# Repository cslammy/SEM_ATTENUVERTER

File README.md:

# SEM_ATTENUVERTER
Audio Attenuverter inspired by classic Tom Oberheim designs

My First experience with an attenuverter--turn a pot CCW, you get increasing amplitude and a signal in phase; CW and you get increasing amplitude with the signal 180 degrees out of phase, was the filter mod pots found an Oberheim SEM. Was I 14 years old? Well, it blew my young mind....Combined with the SEMs multimode filter you can get all sorts of cool sound with the attenuator/inverter + filter, but now, with attenuverters found everywhere, they are, well, everywhere.  This time I used the same core component that made the SEM attenuverter so cool, the somewhat unusual (but not unobtainium) center tapped pot as module's the centerpiece.  Homage to the mighty TO! At noon you get ground--zilch. Turn the pot and you get attenuverter action.  I also added bias offset for each signal, controllable by CV or a set 5V signal. This is an evolving design....it is for +/- 15V "large format" or Frac, but a +/- 12V Euro redesign in is the works.

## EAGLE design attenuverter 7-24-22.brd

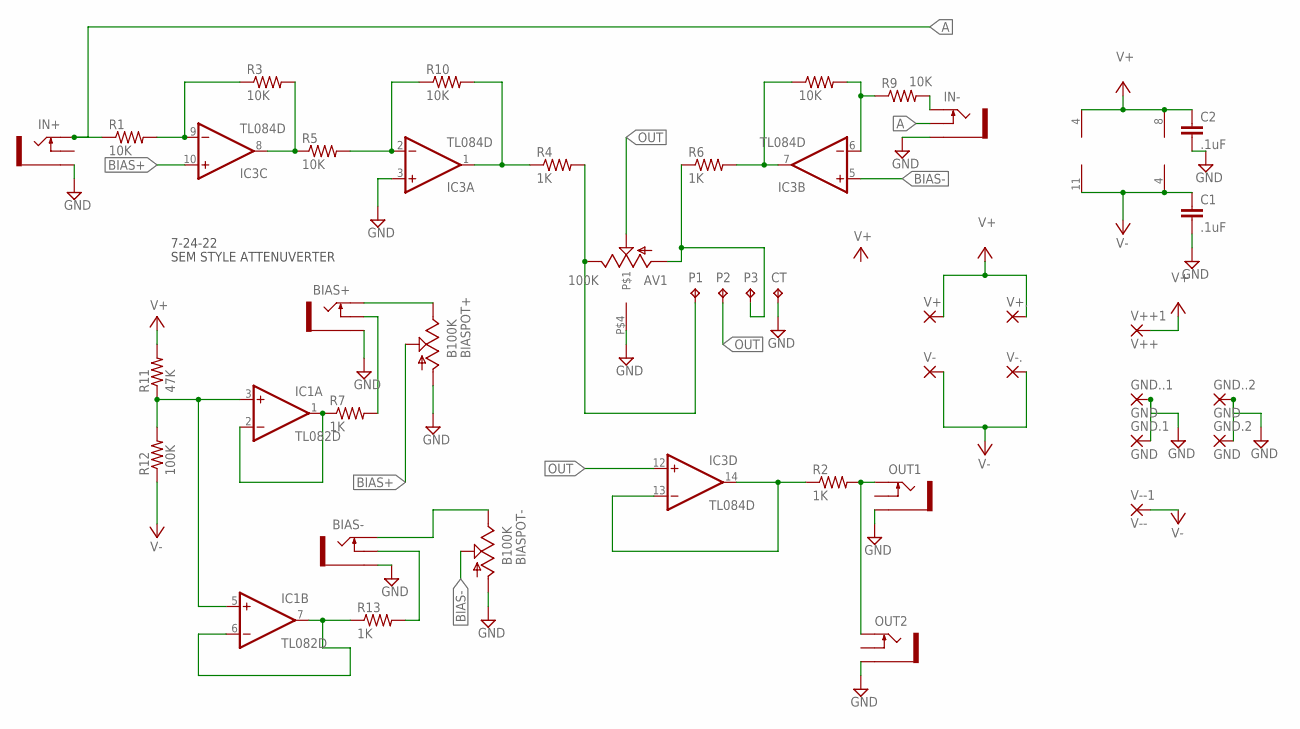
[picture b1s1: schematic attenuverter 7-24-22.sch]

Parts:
AV1: 100K; ALPSCENTERTAP
BIAS+: THONKICONNOLD; THONKICONN
BIAS-: THONKICONNOLD; THONKICONN
BIASPOT+: B100K; 9MM_SNAP-IN_POT
BIASPOT-: B100K; 9MM_SNAP-IN_POT
C1, C2: .1uF; C5B3.5
CT: TPPAD1-13; P1-13
GND.1, GND.2, GND..1, GND..2: GND; 1,6/0,8
IC1: TL082D; SO08
IC3: TL084D; SO14
IN+: THONKICONNOLD; THONKICONN
IN-: THONKICONNOLD; THONKICONN
OUT1, OUT2: THONKICONNOLD; THONKICONN
P1, P2, P3: TPPAD1-13; P1-13
R1, R3, R5, R8, R9, R10: 10K; 0204/7
R2, R4, R6, R7, R13: 1K; 0204/7
R11: 47K; 0204/7
R12: 100K; 0204/7
V+, V+.: WIREPAD2,54/1,1; 2,54/1,1
V++1: V++; 1,6/0,8
V-, V-.: WIREPAD2,54/1,1; 2,54/1,1
V--1: V--; 1,6/0,8

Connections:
A: IN+.P$3_TIP (TIP), IN-.P$2_SWITCH (SWITCH), R1.1
BIAS+: BIASPOT+.2 (S), IC3.10 (+IN)
BIAS-: BIASPOT-.2 (S), IC3.5 (+IN)
GND: AV1.P$4, BIAS+.P$1_SLEEVE (SLEEVE), BIAS-.P$1_SLEEVE (SLEEVE), BIASPOT+.1 (A), BIASPOT-.1 (A), C1.2, C2.2, CT.TP, GND.1.1, GND.2.1, GND..1.1, GND..2.1, IC3.3 (+IN), IN+.P$1_SLEEVE (SLEEVE), IN-.P$1_SLEEVE (SLEEVE), OUT1.P$1_SLEEVE (SLEEVE), OUT2.P$1_SLEEVE (SLEEVE)
unnamed: IC3.6 (-IN), R8.2, R9.1
unnamed: IC1.3 (+IN), IC1.5 (+IN), R11.1, R12.2
unnamed: IC3.7 (OUT), R6.2, R8.1
unnamed: IC1.1 (OUT), IC1.2 (-IN), R7.1
unnamed: AV1.P$1 (HIGH), P1.TP, R4.2
unnamed: IC1.6 (-IN), IC1.7 (OUT), R13.1
unnamed: BIAS-.P$3_TIP (TIP), BIASPOT-.3 (E)
unnamed: IN-.P$3_TIP (TIP), R9.2
unnamed: BIAS+.P$2_SWITCH (SWITCH), R7.2
unnamed: BIAS-.P$2_SWITCH (SWITCH), R13.2
unnamed: IC3.9 (-IN), R1.2, R3.1
unnamed: IC3.13 (-IN), IC3.14 (OUT), R2.1
unnamed: AV1.P$3 (LOW), P3.TP, R6.1
unnamed: BIAS+.P$3_TIP (TIP), BIASPOT+.3 (E)
unnamed: IC3.8 (OUT), R3.2, R5.1
unnamed: IC3.2 (-IN), R5.2, R10.1
unnamed: IC3.1 (OUT), R4.1, R10.2
unnamed: OUT1.P$3_TIP (TIP), OUT2.P$3_TIP (TIP), R2.2
OUT: AV1.P$2 (WIPER), IC3.12 (+IN), P2.TP
V+: C2.1, IC1.8 (V+), IC3.4 (V+), R11.2, V+.1, V++1.1, V+..1
V-: C1.1, IC1.4 (V-), IC3.11 (V-), R12.1, V-.1, V--1.1, V-..1

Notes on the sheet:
SEM STYLE ATTENUVERTER
7-24-22

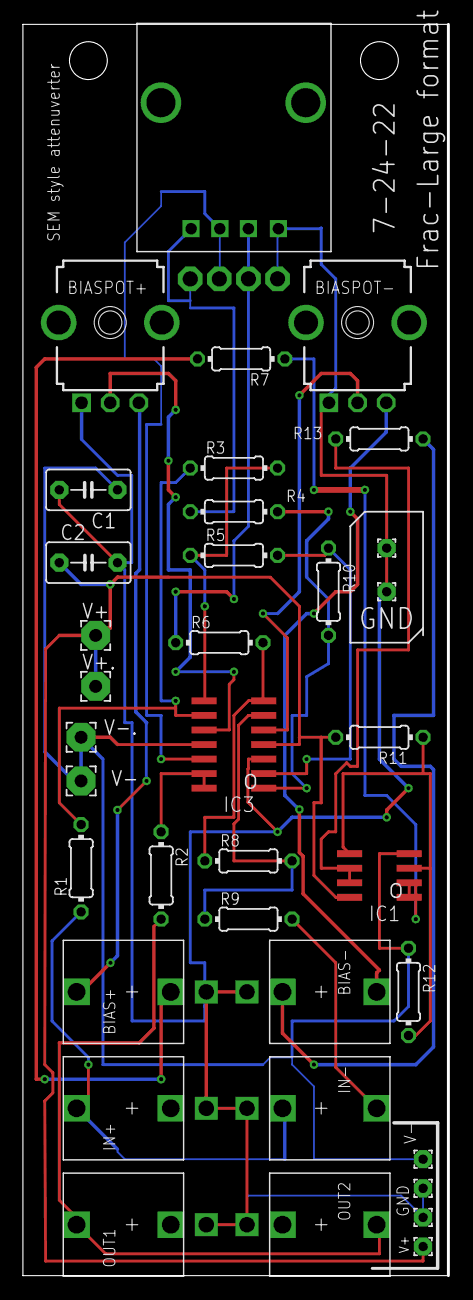
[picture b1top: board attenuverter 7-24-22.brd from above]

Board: 2 copper layers, 37.0 x 109.2 mm, 40 parts (0 on the bottom side), 25 nets.

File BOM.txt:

BOM Large Format/Frac SEM style attenuverter

Part     Value         Device           Package         Description                                                                                                
AV1      100K          ALPSRK11K114     ALPSCENTERTAP   ALPS Pot with center tap ground                                                                                                                   
BIAS+    THONKICONNOLD THONKICONNOLD    THONKICONN      3.5mm socket for Eurorack modular synths                                                                                                          
BIAS-    THONKICONNOLD THONKICONNOLD    THONKICONN      3.5mm socket for Eurorack modular synths                                                                                                          
BIASPOT+ B100K         9MM_SNAP-IN_POT_ 9MM_SNAP-IN_POT "Tall Trimmer"  search on thonk.com                                                                                                
BIASPOT- B100K         9MM_SNAP-IN_POT_ 9MM_SNAP-IN_POT "Tall Trimmer"                                                                                                 
C1       .1uF          C5/3.5           C5B3.5          CAPACITOR                                                                                                                                         
C2       .1uF          C5/3.5           C5B3.5          CAPACITOR                                                                                                                                         
                                                                                                                                  
IC1      TL082D        TL082D           SO08            OP AMP                                                                        
IC3      TL084D        TL084D           SO14            OP AMP                                                                                                                                            
IN+      THONKICONNOLD THONKICONNOLD    THONKICONN      3.5mm socket for Eurorack modular synths                                                                                                          
IN-      THONKICONNOLD THONKICONNOLD    THONKICONN      3.5mm socket for Eurorack modular synths                                                                                                          
OUT1     THONKICONNOLD THONKICONNOLD    THONKICONN      3.5mm socket for Eurorack modular synths                                                                                                          
OUT2     THONKICONNOLD THONKICONNOLD    THONKICONN      3.5mm socket for Eurorack modular synths                                                                                                          
P1       TPPAD1-13     TPPAD1-13        P1-13           Test pad NO NAME                                                                                                                                  
P2       TPPAD1-13     TPPAD1-13        P1-13           Test pad NO NAME                                                                                                                                  
P3       TPPAD1-13     TPPAD1-13        P1-13           Test pad NO NAME                                                                                                                                  
R1       10K           R-US_0204/7      0204/7          RESISTOR, American symbol                                                                                                                         
R2       1K            R-US_0204/7      0204/7          RESISTOR, American symbol                                                                                                                         
R3       10K           R-US_0204/7      0204/7          RESISTOR, American symbol                                                                                                                         
R4       1K            R-US_0204/7      0204/7          RESISTOR, American symbol                                                                                                                         
R5       10K           R-US_0204/7      0204/7          RESISTOR, American symbol                                                                                                                         
R6       1K            R-US_0204/7      0204/7          RESISTOR, American symbol                                                                                                                         
R7       1K            R-US_0204/7      0204/7          RESISTOR, American symbol                                                                                                                         
R8       10K           R-US_0204/7      0204/7          RESISTOR, American symbol                                                                                                                         
R9       10K           R-US_0204/7      0204/7          RESISTOR, American symbol                                                                                                                         
R10      10K           R-US_0204/7      0204/7          RESISTOR, American symbol                                                                                                                         
R11      47K           R-US_0204/7      0204/7          RESISTOR, American symbol                                                                                                                         
R12      100K          R-US_0204/7      0204/7          RESISTOR, American symbol                                                                                                                         
R13      1K            R-US_0204/7      0204/7          RESISTOR, American symbol

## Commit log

2022-09-23 Initial upload
    This is for FRAC and large format modular synthesizers. Does not include a front panel. See the blog post here for more information.
    https://audiodiwhy.blogspot.com/2022/09/again-few-years-ago-i-designed-laid-out.html
2022-09-23 Eagle Files 7-22-22 revision
2022-09-23 Fill out README
